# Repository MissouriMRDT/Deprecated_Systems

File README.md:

<<<<<<< HEAD
# Deprecated-Systems
 Deprecated sub-system repositories that have no present day equivalent

How to add repos to this: 

1) Make branch on here for the repo you're about to copy in
2) Clone this repo onto your pc
3) Make sure that you've merged all branches on the deprecated repo into master, this process only preserves its master
4) in gitshell inside of the Deprecated-Systems folder:

git checkout [name of branch you're going to copy the repo into]

git remote add x [url of deprecated repo]

git fetch x

git merge x/master --allow-unrelated-histories

git remote rm x

5) delete old branch

=======
Battery-Management-System
=========================

Battery Management System with integrated CC and CV charge control and passive cell balancing.
>>>>>>> x/master

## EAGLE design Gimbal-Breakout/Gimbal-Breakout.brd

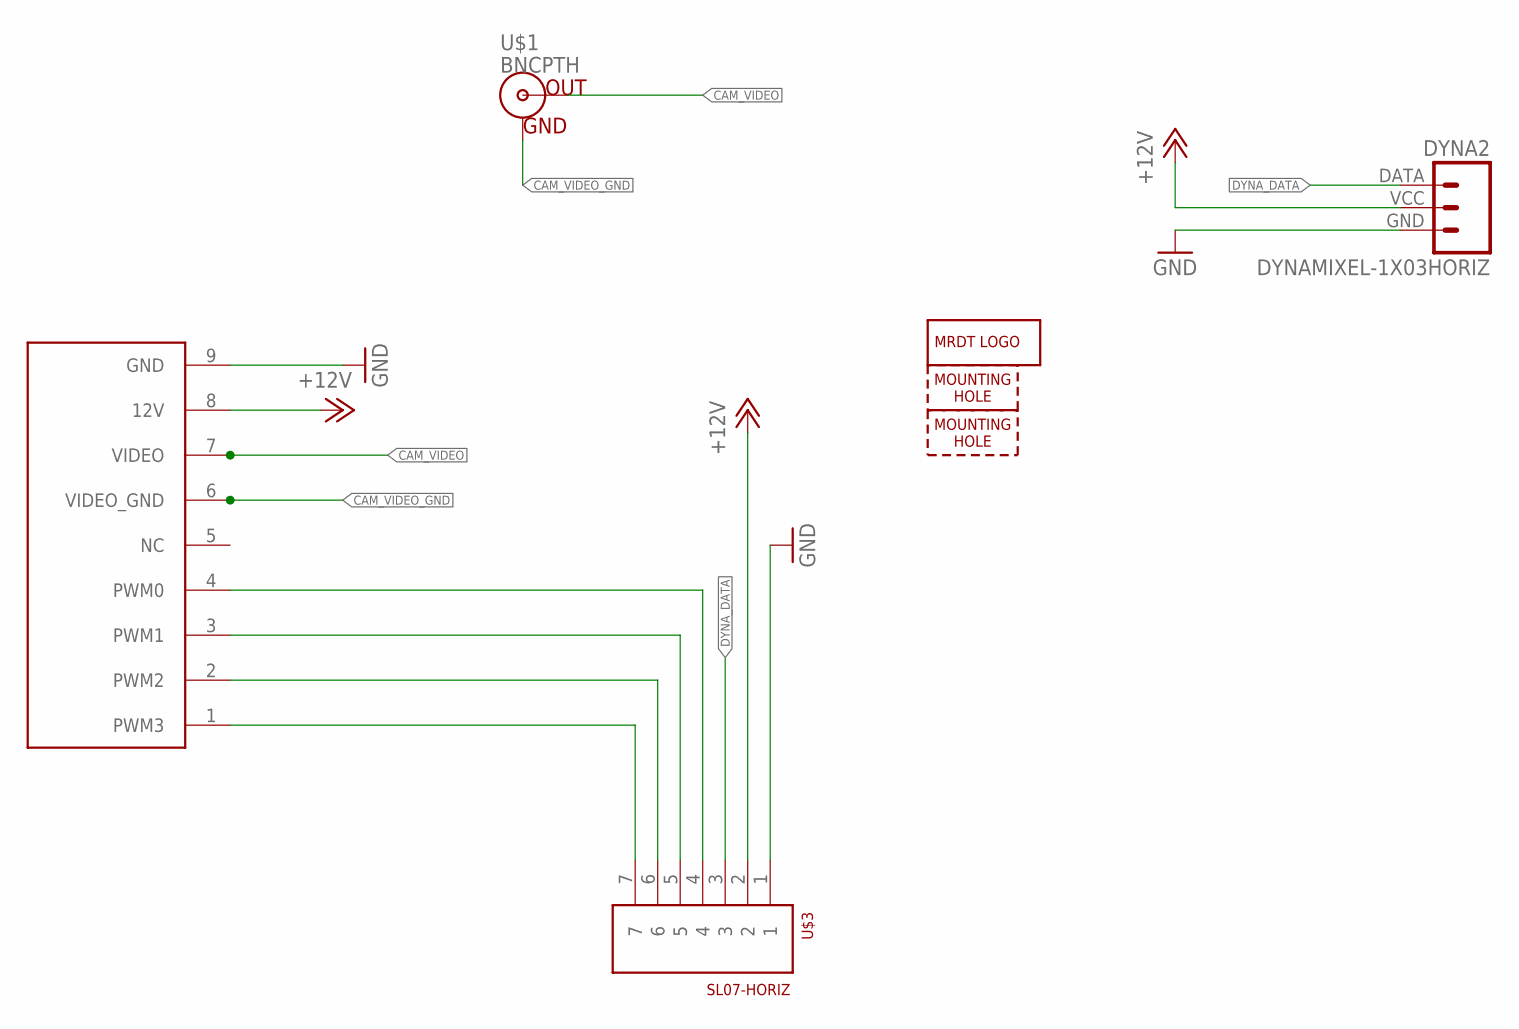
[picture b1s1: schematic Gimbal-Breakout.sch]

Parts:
DYNA2: DYNAMIXEL-1X03HORIZ; MLX-SPOX5268-3PIN
H1, H2: MOUNTING_HOLE#4; #4_SCREW
LOGO1: MRDT_LOGO
U$1: BNCPTH; BNC
U$3: SL07-HORIZ; MOLEX-70551-0006
U$4: CAMERA_BREAKOUT; CAM_CONNECTOR

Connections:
+12V: DYNA2.VCC, U$3.2, U$4.8 (12V)
CAM_PWM0: U$3.4, U$4.4 (PWM0)
CAM_PWM1: U$3.5, U$4.3 (PWM1)
CAM_PWM2: U$3.6, U$4.2 (PWM2)
CAM_PWM3: U$3.7, U$4.1 (PWM3)
CAM_VIDEO: U$1.S (OUT), U$4.7 (VIDEO)
CAM_VIDEO_GND: U$1.GND, U$4.6 (VIDEO_GND)
DYNA_DATA: DYNA2.DATA, U$3.3
GND: DYNA2.GND, U$3.1, U$4.9 (GND)

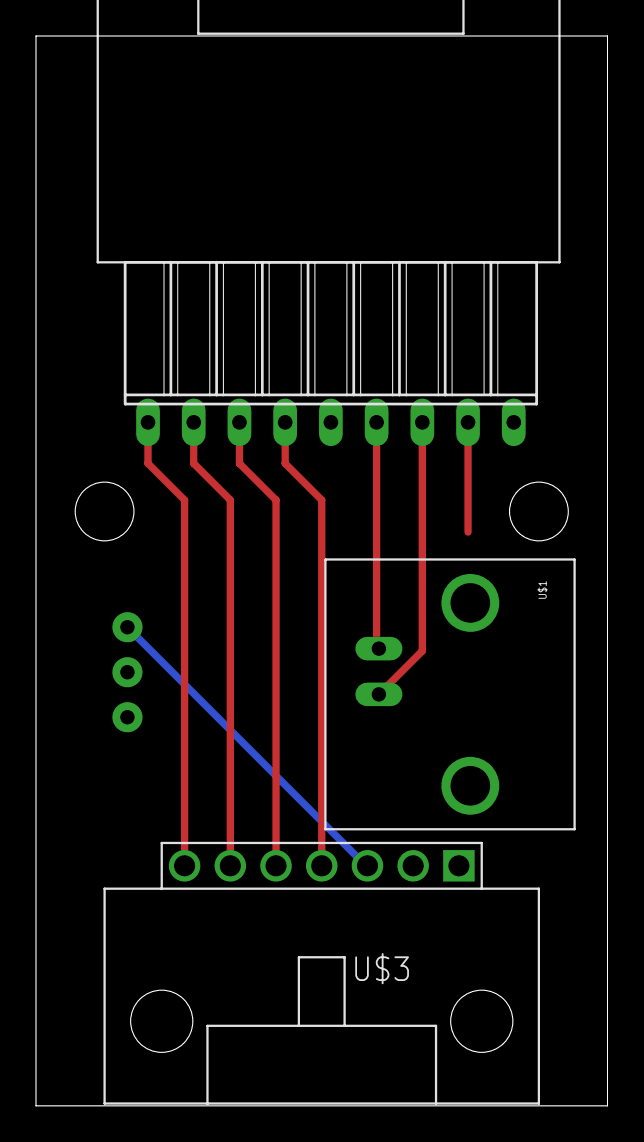
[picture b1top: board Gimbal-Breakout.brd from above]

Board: 2 copper layers, 31.8 x 59.4 mm, 7 parts (1 on the bottom side), 9 nets.

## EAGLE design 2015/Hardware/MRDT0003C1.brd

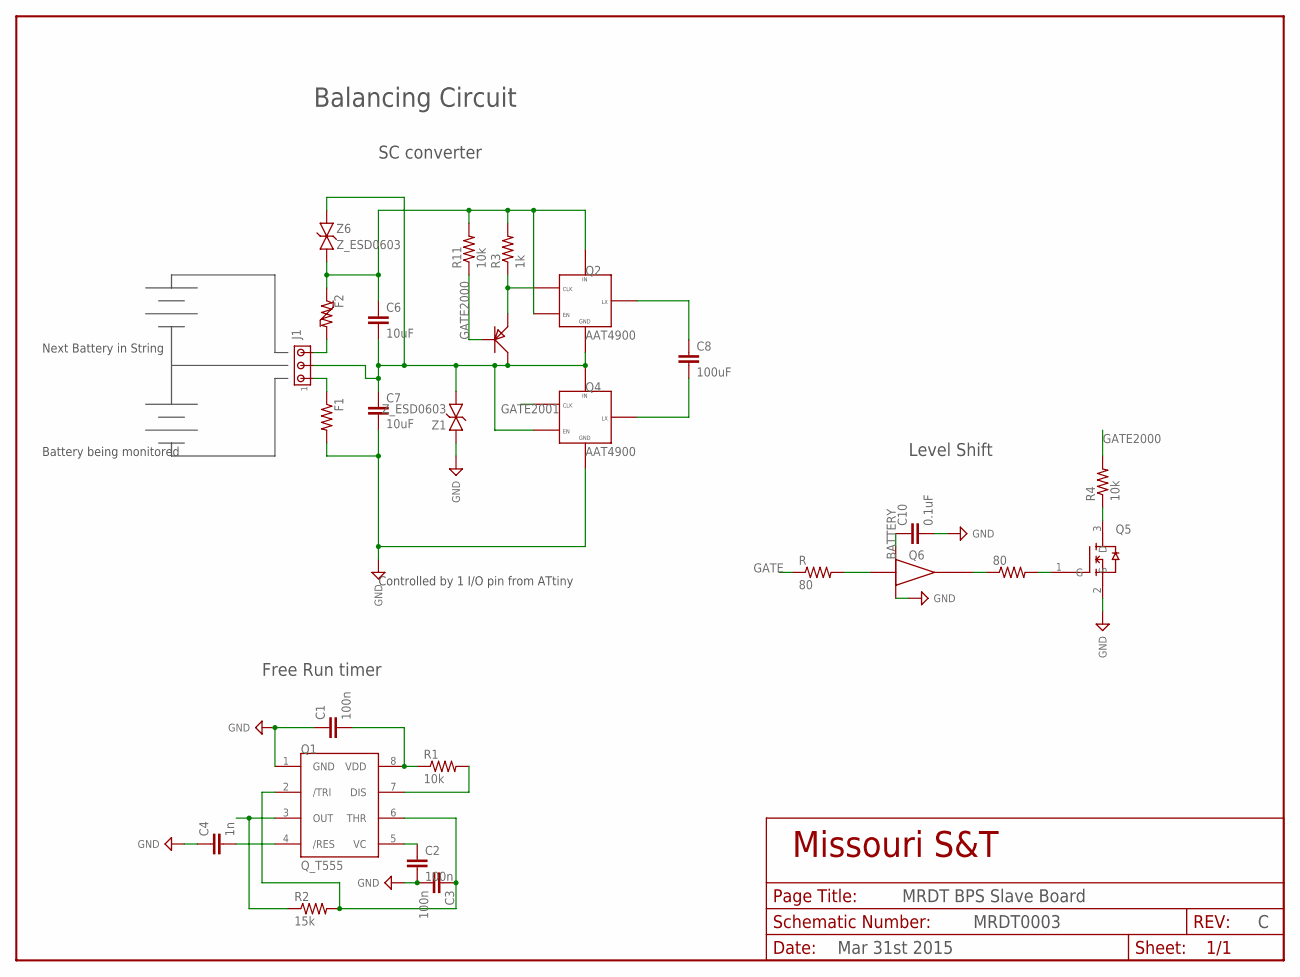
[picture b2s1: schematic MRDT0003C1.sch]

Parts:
80: R_RES_1206; R_1206
C1, C2, C3: 100n; C_0603
C4: 1n; C_0603
C6, C7: 10uF; C_1206
C8: 100uF; C_1206
C10: 0.1uF; C_0603
F1, F2: R_RES_1210; R_1210
J1: J_HDR1X3_BRK_100MIL; J_BRK1X3_100MIL
Q1: Q_T555; SOIC8
Q2, Q4: AAT4900; SOT-23-5
Q5: N-CH-MOSFETSOT-23; SOT-23
Q6: Q_INVERTERSOT-23-5; SOT-23-5
Q7: Q_PNP; SOT-23
R: 80; R_0603
R1, R4, R11: 10k; R_0603
R2: 15k; R_0603
R3: 1k; R_0603
Z1, Z6: Z_ESD0603; 0603

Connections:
BATTERY: C1.2, C4.2, C6.2, C7.1, C10.1, J1.2, Q1.4 (/RES), Q1.8 (VDD), Q2.2 (GND), Q4.3 (EN), Q4.5 (IN), Q6.5 (VCC), Q7.3 (C), R1.1, Z1.1, Z6.2
GATE: Q1.3 (OUT), R.1, R2.1
GATE2000: Q7.1 (B), R4.2, R11.1
GATE2001: Q4.4 (CLK), Q6.2 (A), R.2
GND: C1.1, C2.2, C3.2, C4.1, C7.2, C10.2, F1.2, Q1.1 (GND), Q4.2 (GND), Q5.2 (S), Q6.3 (GND), Z1.2
unnamed: Q2.4 (CLK), Q7.2 (E), R3.1
unnamed: F2.2, J1.3
unnamed: C8.1, Q2.1 (LX)
unnamed: C8.2, Q4.1 (LX)
unnamed: F1.1, J1.1
unnamed: Q1.7 (DIS), R1.2
unnamed: Q5.3 (D), R4.1
unnamed: 80.1, Q6.4 (Y)
unnamed: 80.2, Q5.1 (G)
unnamed: C6.1, F2.1, Q2.3 (EN), Q2.5 (IN), R3.2, R11.2, Z6.1
unnamed: C3.1, Q1.2 (/TRI), Q1.6 (THR), R2.2
unnamed: C2.1, Q1.5 (VC)

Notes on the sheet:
Battery being monitored
Next Battery in String
Controlled by 1 I/O pin from ATtiny
Balancing Circuit
SC converter
Level Shift
MRDT BPS Slave Board
MRDT0003
Mar 31st 2015
Free Run timer

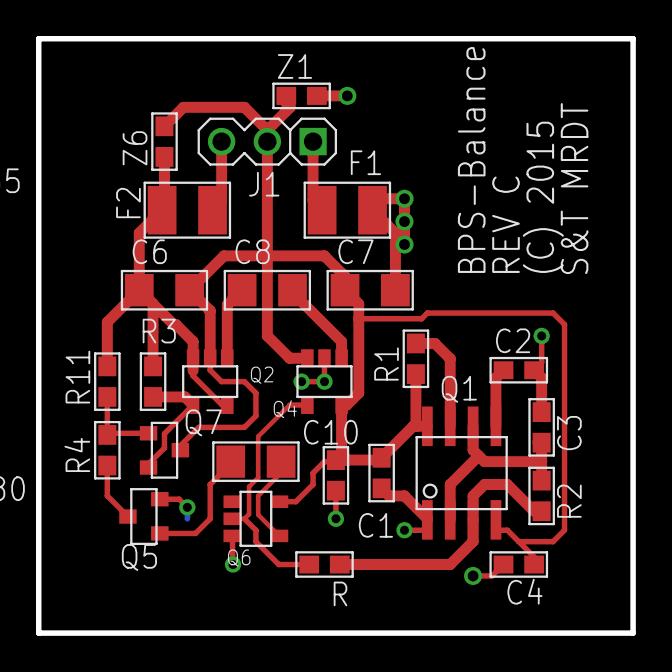
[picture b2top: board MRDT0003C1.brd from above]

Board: 2 copper layers, 33.0 x 33.0 mm, 26 parts (0 on the bottom side), 17 nets.

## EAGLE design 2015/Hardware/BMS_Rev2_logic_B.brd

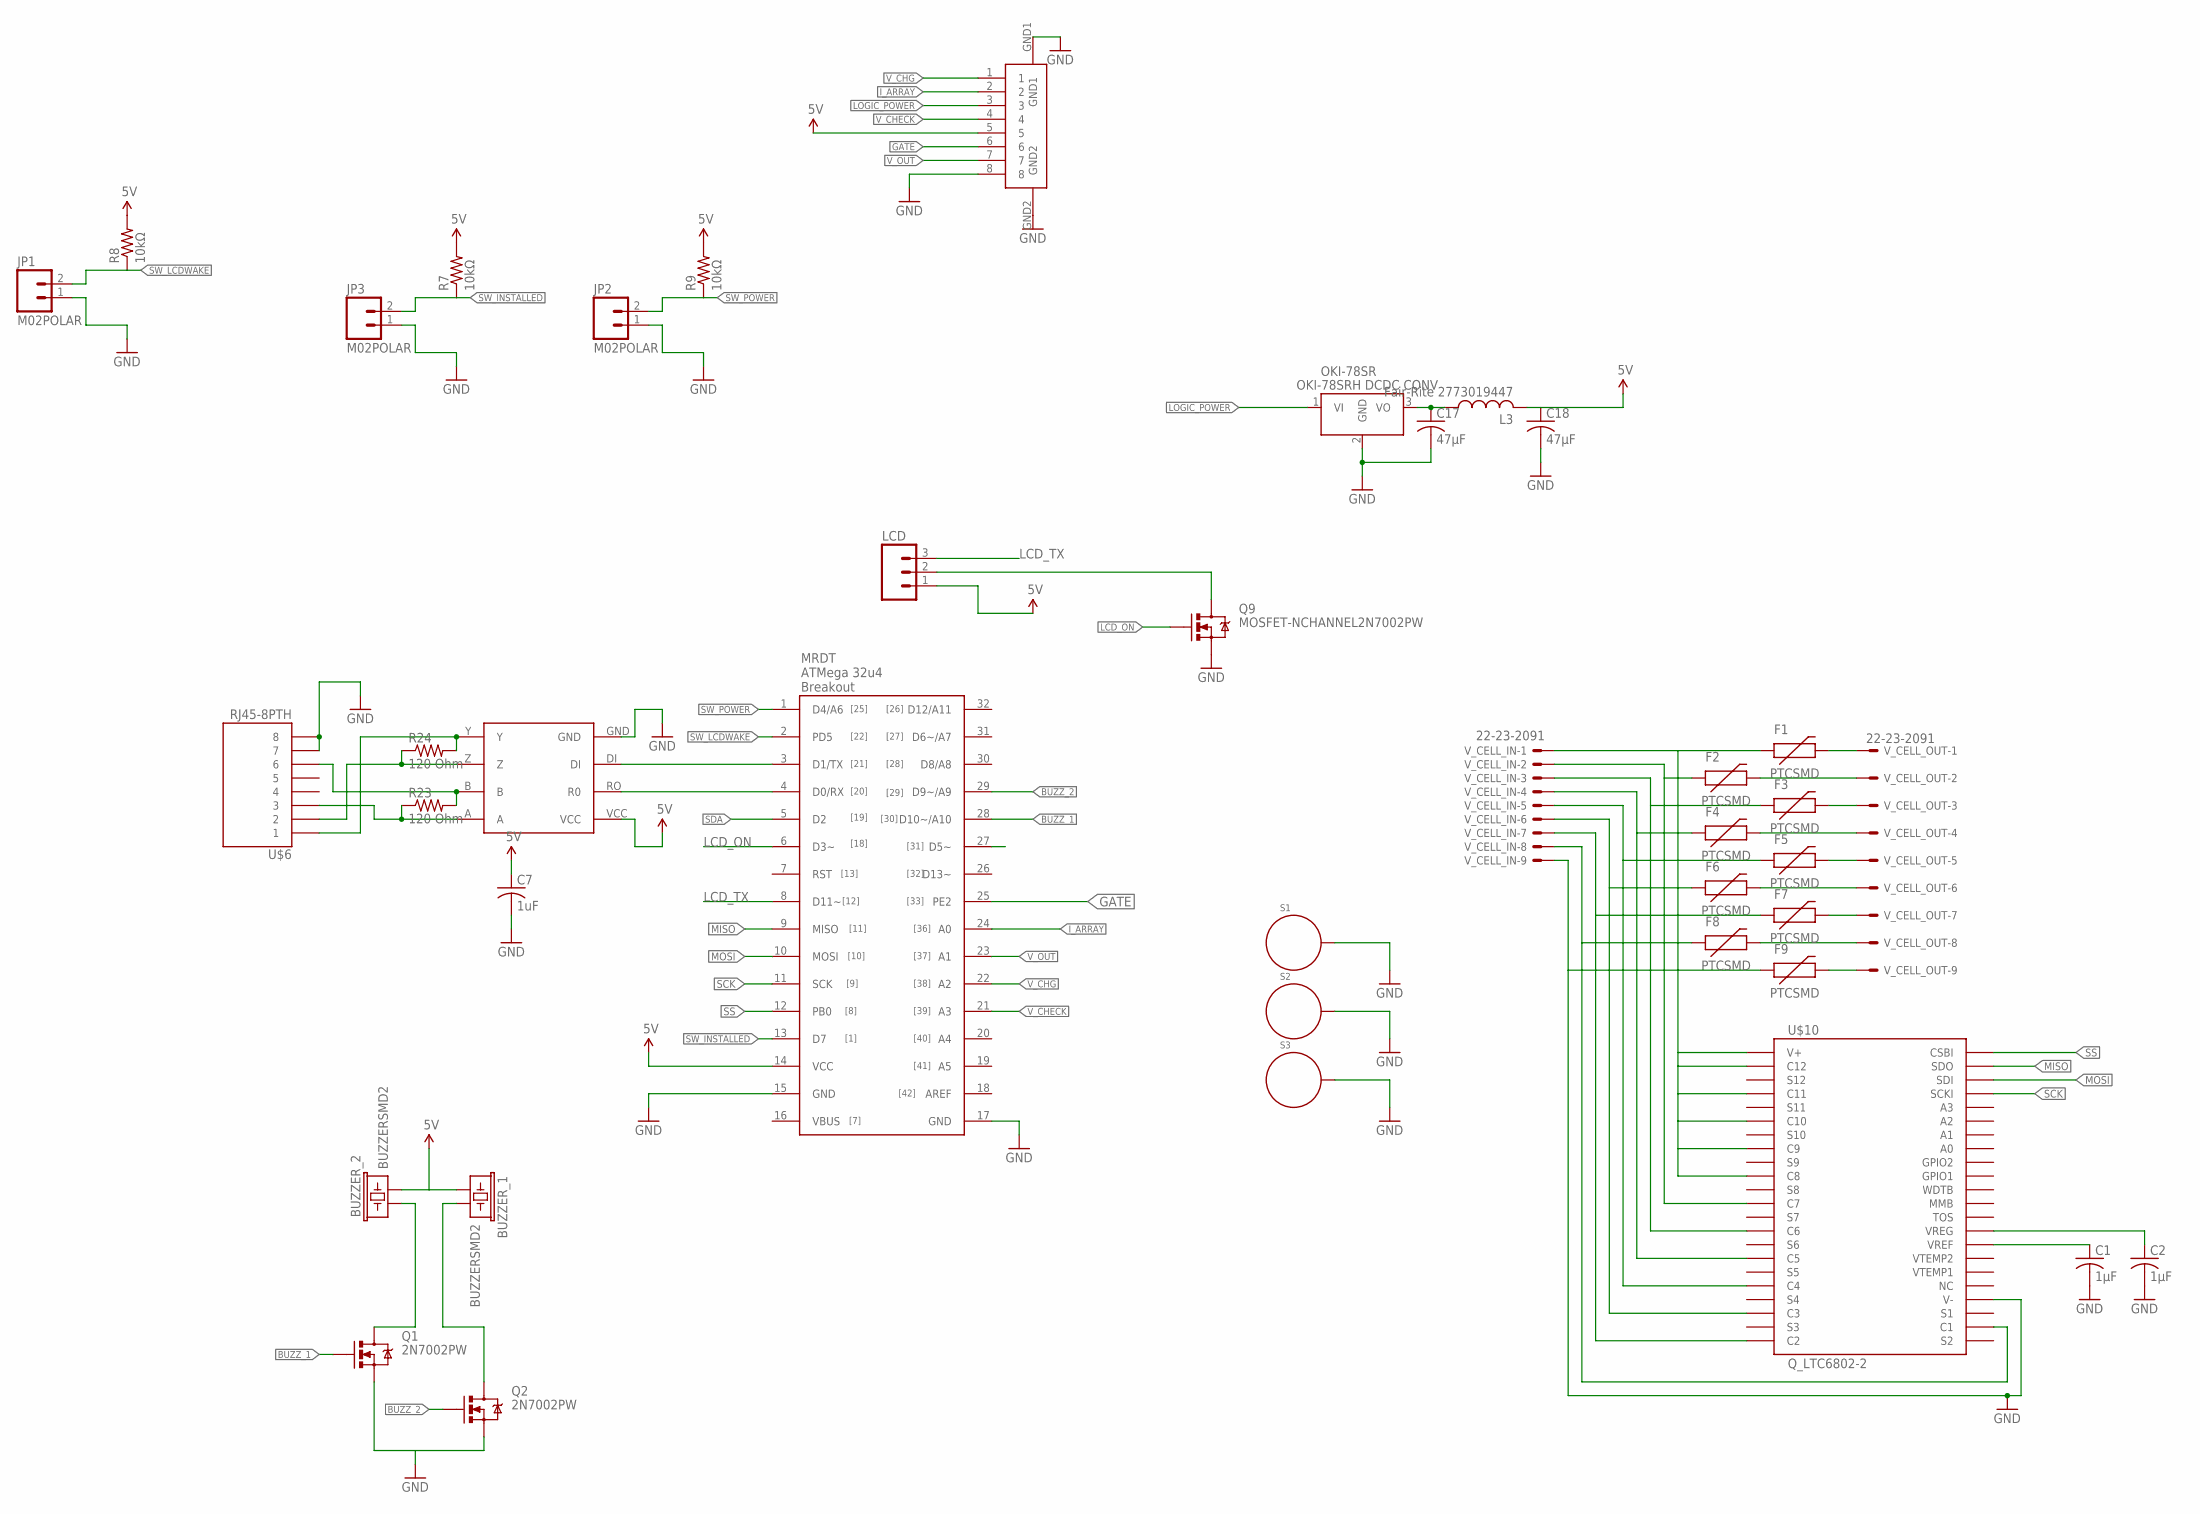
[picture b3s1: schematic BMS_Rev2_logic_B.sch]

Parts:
BUZZER_1, BUZZER_2: BUZZERSMD2; BUZZER-CCV
C1, C2: 1µF; C1206
C7: 1uF; C1206
C17, C18: 47µF; C1206
F1, F2, F3, F4, F5, F6, F7, F8, F9: PTCSMD; PTC-1206
JP1, JP2, JP3: M02POLAR; MOLEX-1X2
L3: Fair-Rite 2773019447; L4532M
LCD: M03POLAR; MOLEX-1X3
OKI-78SR: Q_OKI-78SR; OKI-78SRH
Q1, Q2: 2N7002PW; SOT323
Q9: MOSFET-NCHANNEL2N7002PW; SOT323
R7, R8, R9: 10kΩ; R1206
R23, R24: 120 Ohm; 1206
S1, S2, S3: STANDOFF_ELECTRICAL; STANDOFF-ELECTRICAL
U$1: 8POS_LOGIC; LOGIC_CONNECT
U$3: 32U4_BREAKOUT; 32U4_MCU_DIP
U$6: RJ45-8PTH; RJ45-8
U$9: MAX3077; MAX3070E
U$10: Q_LTC6802-2; SSOP44
V_CELL_IN: 22-23-2091
V_CELL_OUT: 22-23-2091

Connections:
5V: BUZZER_1.+ (1), BUZZER_2.- (2), C7.1, C18.1, L3.2, LCD.1, R7.2, R8.2, R9.2, U$1.5, U$3.14 (VCC), U$9.VCC
BUZZ_1: Q1.1 (G), U$3.28 (D10~/A10)
BUZZ_2: Q2.1 (G), U$3.29 (D9~/A9)
GATE: U$1.6, U$3.25 (PE2)
GND: C1.2, C2.2, C7.2, C17.2, C18.2, F9.1, JP1.1, JP2.1, JP3.1, OKI-78SR.2 (GND), Q1.2 (S), Q2.2 (S), Q9.2 (S), S1.P1, S2.P1, S3.P1, U$1.8, U$1.GND1, U$1.GND2, U$3.15 (GND), U$3.17 (GND), U$6.7, U$6.8, U$9.GND, U$10.26 (V-), V_CELL_IN.9
I_ARRAY: U$1.2, U$3.24 (A0)
LCD_DB4: U$3.27 (D5~)
LCD_ON: Q9.1 (G), U$3.6 (D3~)
LCD_TX: LCD.3, U$3.8 (D11~)
LOGIC_POWER: OKI-78SR.1 (VI), U$1.3
MISO: U$3.9 (MISO), U$10.43 (SDO)
MOSI: U$3.10 (MOSI), U$10.42 (SDI)
unnamed: F1.2, V_CELL_OUT.1
unnamed: F2.2, V_CELL_OUT.2
unnamed: F3.2, V_CELL_OUT.3
unnamed: F9.2, V_CELL_OUT.9
unnamed: LCD.2, Q9.3 (D)
unnamed: R24.2, U$6.1, U$9.Y
unnamed: R24.1, U$6.2, U$9.Z
unnamed: BUZZER_1.- (2), Q2.3 (D)
unnamed: R23.2, U$6.6, U$9.B
unnamed: R23.1, U$6.3, U$9.A
unnamed: U$3.3 (D1/TX), U$9.DI
unnamed: C1.1, U$10.30 (VREF)
unnamed: C2.1, U$10.31 (VREG)
unnamed: F4.2, V_CELL_OUT.4
unnamed: F5.2, V_CELL_OUT.5
unnamed: F6.2, V_CELL_OUT.6
unnamed: F7.2, V_CELL_OUT.7
unnamed: F8.2, V_CELL_OUT.8
unnamed: BUZZER_2.+ (1), Q1.3 (D)
unnamed: F1.1, U$10.1 (V+), U$10.2 (C12), U$10.4 (C11), U$10.6 (C10), U$10.8 (C9), U$10.10 (C8), V_CELL_IN.1
unnamed: F2.1, U$10.12 (C7), V_CELL_IN.2
unnamed: F3.1, U$10.14 (C6), V_CELL_IN.3
unnamed: F6.1, U$10.20 (C3), V_CELL_IN.6
unnamed: F7.1, U$10.22 (C2), V_CELL_IN.7
unnamed: F8.1, U$10.24 (C1), V_CELL_IN.8
unnamed: F4.1, U$10.16 (C5), V_CELL_IN.4
unnamed: F5.1, U$10.18 (C4), V_CELL_IN.5
unnamed: C17.1, L3.1, OKI-78SR.3 (VO)
RXD: U$3.4 (D0/RX), U$9.RO (R0)
SCK: U$3.11 (SCK), U$10.41 (SCKI)
SDA: U$3.5 (D2)
SS: U$3.12 (PB0), U$10.44 (CSBI)
SW_INSTALLED: JP3.2, R7.1, U$3.13 (D7)
SW_LCDWAKE: JP1.2, R8.1, U$3.2 (PD5)
SW_POWER: JP2.2, R9.1, U$3.1 (D4/A6)
V_CHECK: U$1.4, U$3.21 (A3)
V_CHG: U$1.1, U$3.22 (A2)
V_OUT: U$1.7, U$3.23 (A1)

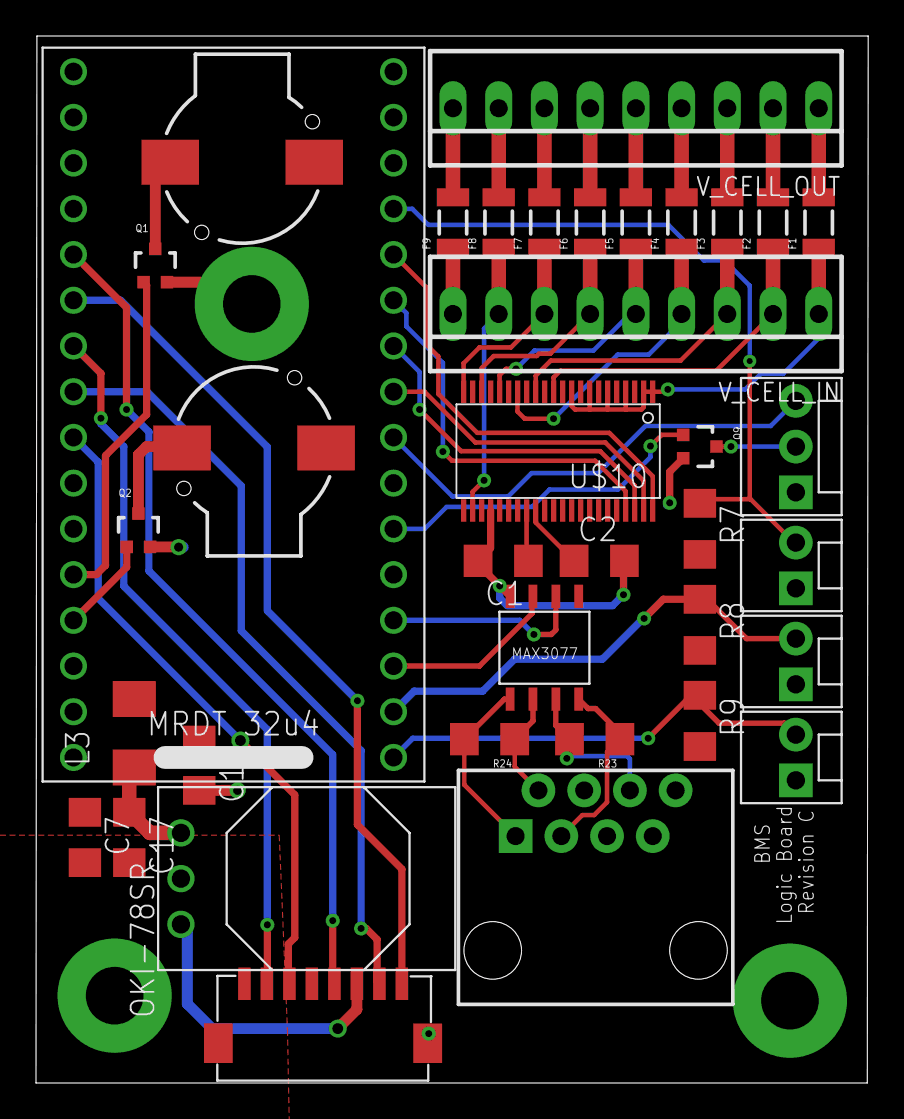
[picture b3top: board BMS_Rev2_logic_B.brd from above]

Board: 2 copper layers, 46.2 x 58.2 mm, 40 parts (0 on the bottom side), 48 nets.

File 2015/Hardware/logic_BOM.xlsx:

Quantity | Value | Device | Package | DigiKey ID
1 |  | L-USL3216C
1 | 32U4_BREAKOUT | 32U4_BREAKOUT
1 | MAX3077 | MAX3077 |  | MAX3077EESA+-ND
1 | MOSFET-NCHANNEL2N7002PW | MOSFET-NCHANNEL2N7002PW |  | 568-5987-1-ND
1 | Q_LTC6802-2 | Q_LTC6802-2 |  | LTC6802IG-2#PBF-ND
1 | Q_OKI-78SR | Q_OKI-78SR |  | 811-2692-ND
1 | RJ45-8PTH | RJ45-8PTH |  | 609-1046-ND
2 | 120 Ohm | RESISTOR1206 |  | P120ECT-ND
3 | 1uF | C-USC1206 |  | 445-1592-1-ND
2 | 22-23-2091 | 22-23-2091 |  | WM4207-ND
2 | 47uF | C-USC1206 |  | 490-5528-1-ND
2 |  | BUZZERSMD2 |  | 102-1265-1-ND
3 | 10k | R-US_R1206 |  | P10KECT-ND
9 |  | PTCSMD |  | 283-3134-1-ND

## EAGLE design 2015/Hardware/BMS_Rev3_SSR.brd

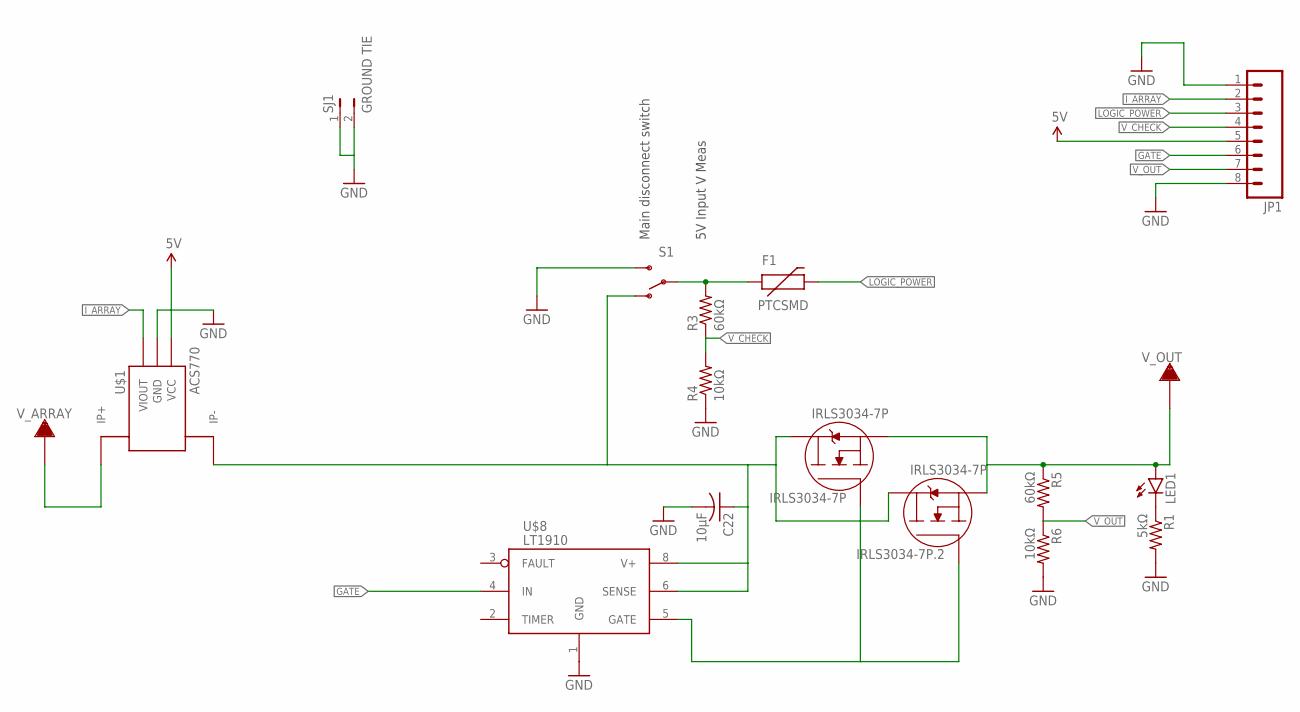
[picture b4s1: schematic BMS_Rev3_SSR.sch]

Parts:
C22: 10µF; C1206
F1: PTCSMD; PTC-1206
IRLS3034-7P, IRLS3034-7P.2: IRLS3034-7P; D2PAK-7
JP1: M08BM08B-SRSS-TB; BM08B-SRSS-TB
LED1: LED1206; LED-1206
R1: 5kΩ; R1206
R3, R5: 60kΩ; R1206
R4, R6: 10kΩ; R1206
S1: SWITCH-SPDTPTH; SWITCH-SPDT
SJ1: GROUND TIE; PTH-JUMPER-2-NO_NO_SILK
U$1: ACS770; PFF_LEADFORM
U$8: LT1910; SO8
V_ARRAY: TERMINAL_HOLE; LARGE_TERMINAL_HOLE
V_OUT: TERMINAL_HOLE; LARGE_TERMINAL_HOLE

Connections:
5V: JP1.5, U$1.1 (VCC)
GATE: JP1.6, U$8.4 (IN)
GND: C22.2, JP1.1, JP1.8, R1.2, R4.1, R6.2, S1.3 (S), SJ1.1, SJ1.2, U$1.2 (GND), U$8.1 (GND)
I_ARRAY: JP1.2, U$1.3 (VIOUT)
LOGIC_POWER: F1.2, JP1.3
unnamed: IRLS3034-7P.2 (SOURCE), IRLS3034-7P.3 (SOURCE), IRLS3034-7P.4 (SOURCE), IRLS3034-7P.5 (SOURCE), IRLS3034-7P.6 (SOURCE), IRLS3034-7P.2.2 (SOURCE), IRLS3034-7P.2.3 (SOURCE), IRLS3034-7P.2.4 (SOURCE), IRLS3034-7P.2.5 (SOURCE), IRLS3034-7P.2.6 (SOURCE), LED1.A, R5.1, V_OUT.P$1
unnamed: U$1.4_1 (IP+), U$1.4_2 (IP+), U$1.4_3 (IP+), U$1.4_4 (IP+), U$1.4_5 (IP+), U$1.4_6 (IP+), U$1.4_7 (IP+), U$1.4_8 (IP+), U$1.4_9 (IP+), U$1.4_10 (IP+), U$1.4_11 (IP+), U$1.4_12 (IP+), U$1.4_13 (IP+), U$1.4_14 (IP+), U$1.4_15 (IP+), U$1.4_16 (IP+), U$1.4_B (IP+), U$1.4_T (IP+), V_ARRAY.P$1
unnamed: C22.1, IRLS3034-7P.PAD (DRAIN), IRLS3034-7P.2.PAD (DRAIN), S1.1 (O), U$1.5_1 (IP-), U$1.5_2 (IP-), U$1.5_3 (IP-), U$1.5_4 (IP-), U$1.5_5 (IP-), U$1.5_6 (IP-), U$1.5_7 (IP-), U$1.5_8 (IP-), U$1.5_9 (IP-), U$1.5_10 (IP-), U$1.5_11 (IP-), U$1.5_12 (IP-), U$1.5_13 (IP-), U$1.5_14 (IP-), U$1.5_15 (IP-), U$1.5_16 (IP-), U$1.5_B (IP-), U$1.5_T (IP-), U$8.6 (SENSE), U$8.8 (V+)
unnamed: LED1.C, R1.1
unnamed: IRLS3034-7P.1 (GATE), IRLS3034-7P.2.1 (GATE), U$8.5 (GATE)
unnamed: F1.1, R3.2, S1.2
V_CHECK: JP1.4, R3.1, R4.2
V_OUT: JP1.7, R5.2, R6.1

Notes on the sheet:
5V Input V Meas
Main disconnect switch

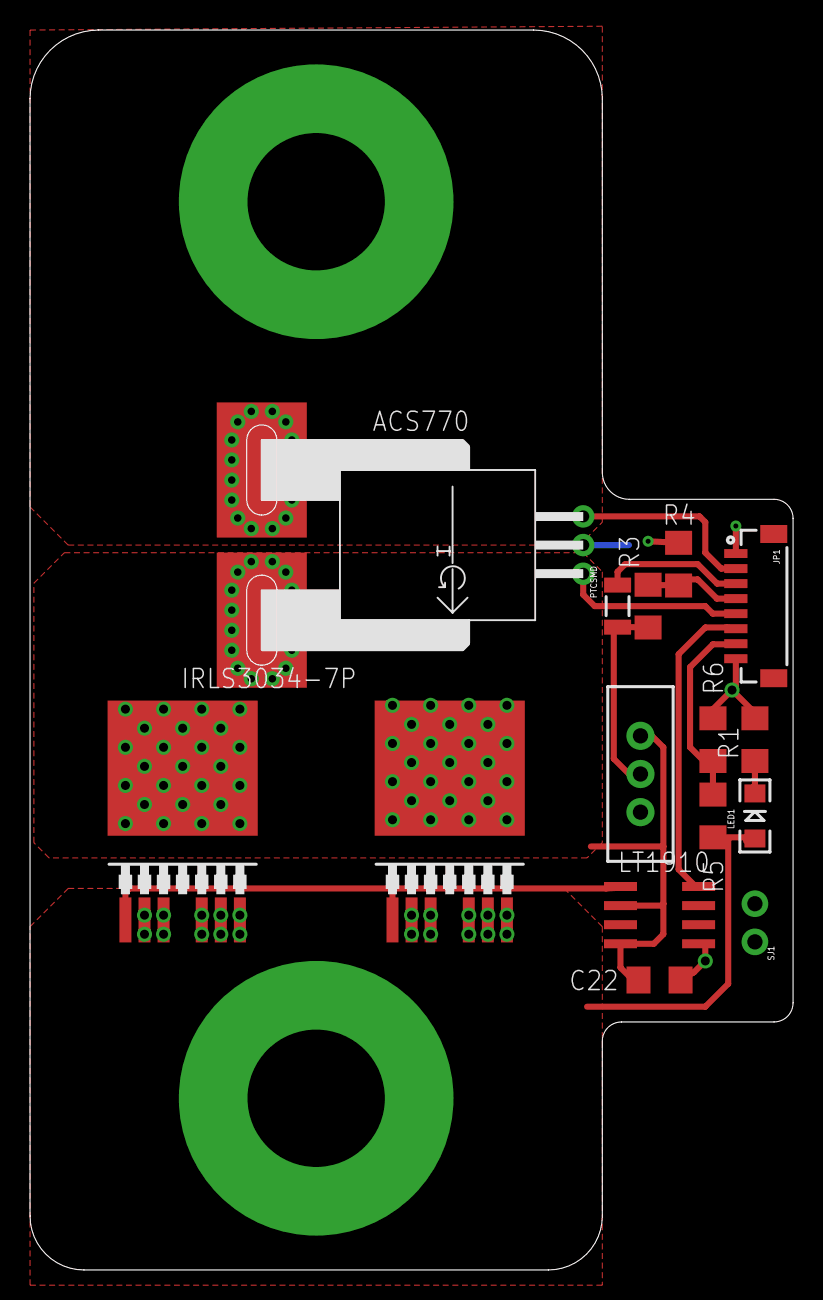
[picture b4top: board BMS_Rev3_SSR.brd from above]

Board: 2 copper layers, 50.8 x 82.5 mm, 17 parts (0 on the bottom side), 13 nets.

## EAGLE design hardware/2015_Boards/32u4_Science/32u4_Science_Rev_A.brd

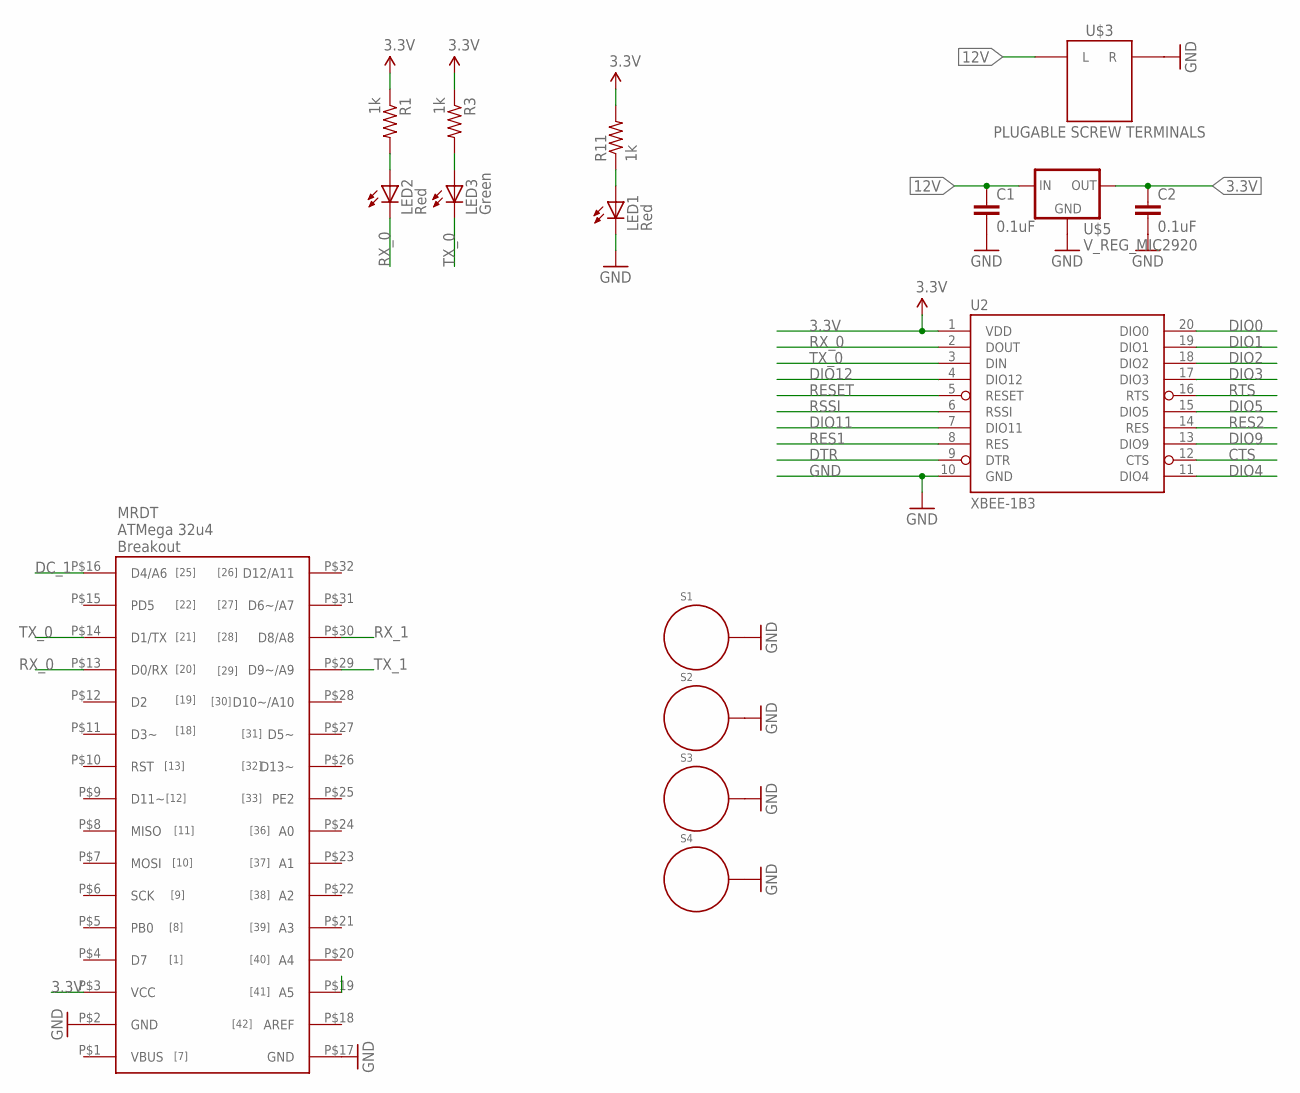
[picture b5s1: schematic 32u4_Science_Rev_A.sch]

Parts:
C1, C2: 0.1uF; 1206
LED1, LED2: Red; LED-0603
LED3: Green; LED-0603
R1, R3, R11: 1k; 1206
S1, S2, S3, S4: STANDOFF_ELECTRICAL; STANDOFF-ELECTRICAL
U2: XBEE-1B3; XBEE-SMD
U$1: 32U4_BREAKOU_SMD; 32U3_MCU_DIP_SMD
U$3: PLUGABLE SCREW TERMINALS; 691321100002
U$5: V_REG_MIC2920; SOT223

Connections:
3.3V: C2.1, R1.1, R3.1, R11.2, U2.1 (VDD), U$1.P$3 (VCC), U$5.3 (OUT)
12V: C1.1, U$3.L, U$5.1 (IN)
CTS: U2.12 (CTS)
DC_1: U$1.P$16 (D4/A6)
DIO0: U2.20 (DIO0)
DIO1: U2.19 (DIO1)
DIO2: U2.18 (DIO2)
DIO3: U2.17 (DIO3)
DIO4: U2.11 (DIO4)
DIO5: U2.15 (DIO5)
DIO9: U2.13 (DIO9)
DIO11: U2.7 (DIO11)
DIO12: U2.4 (DIO12)
DTR: U2.9 (DTR)
GND: C1.2, C2.2, LED1.C, S1.P1, S2.P1, S3.P1, S4.P1, U2.10 (GND), U$1.P$2 (GND), U$1.P$17 (GND), U$3.R, U$5.2 (GND), U$5.4 (GND)
unnamed: LED2.A, R1.2
unnamed: LED3.A, R3.2
unnamed: LED1.A, R11.1
RES1: U2.8 (RES)
RES2: U2.14 (RES)
RESET: U2.5 (RESET)
RSSI: U2.6 (RSSI)
RTS: U2.16 (RTS)
RX_0: LED2.C, U2.2 (DOUT), U$1.P$13 (D0/RX)
RX_1: U$1.P$30 (D8/A8)
TX_0: LED3.C, U2.3 (DIN), U$1.P$14 (D1/TX)
TX_1: U$1.P$29 (D9~/A9)

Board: 2 copper layers, 16 parts (1 on the bottom side), 8 nets, no tracks yet.

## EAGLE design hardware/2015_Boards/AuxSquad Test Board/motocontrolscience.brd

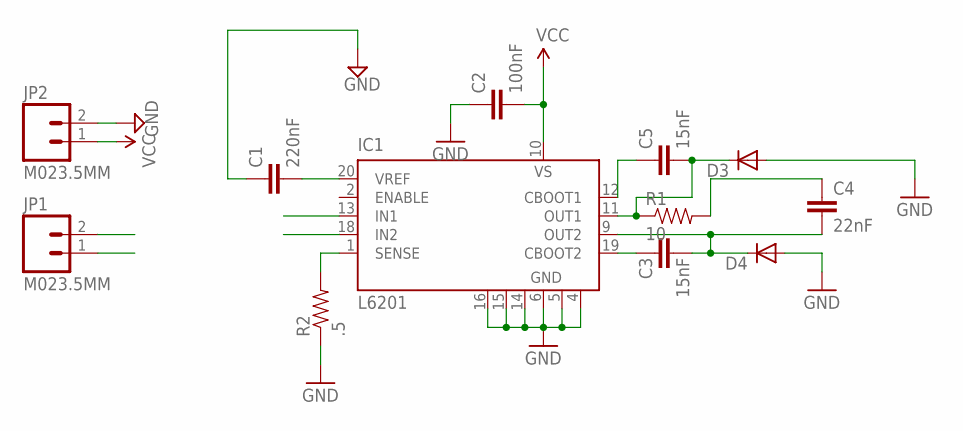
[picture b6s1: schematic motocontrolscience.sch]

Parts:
C1: 220nF; 1206
C2: 100nF; 1206
C3, C5: 15nF; 1206
C4: 22nF; 1206
D3, D4: DIODE-DO214BA; DO214BA
IC1: L6201; SO20
JP1, JP2: M023.5MM; SCREWTERMINAL-3.5MM-2
R1: 10; 1206
R2: .5; 1206

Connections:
GND: C1.1, C2.1, D3.A, D4.A, IC1.4 (GND), IC1.5 (GND), IC1.6 (GND), IC1.14 (GND), IC1.15 (GND), IC1.16 (GND), JP2.2, R2.1
unnamed: C3.1, IC1.19 (CBOOT2)
unnamed: C4.1, R1.2
unnamed: C5.1, IC1.12 (CBOOT1)
unnamed: C1.2, IC1.20 (VREF)
unnamed: IC1.1 (SENSE), R2.2
OUT1: C5.2, D3.C, IC1.11 (OUT1), JP1.1, R1.1
OUT2: C3.2, C4.2, D4.C, IC1.9 (OUT2), JP1.2
VCC: C2.2, IC1.10 (VS), JP2.1

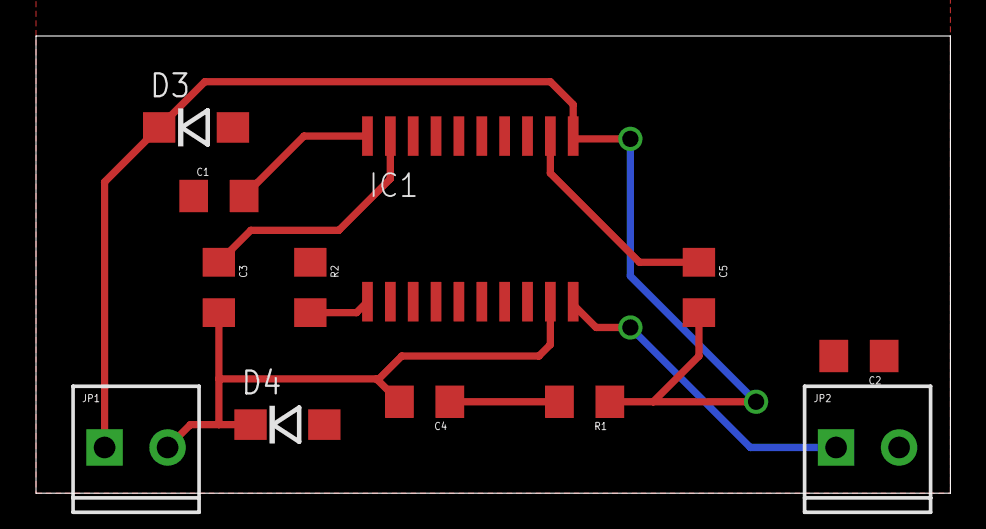
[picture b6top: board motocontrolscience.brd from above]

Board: 2 copper layers, 50.8 x 25.4 mm, 12 parts (0 on the bottom side), 9 nets.

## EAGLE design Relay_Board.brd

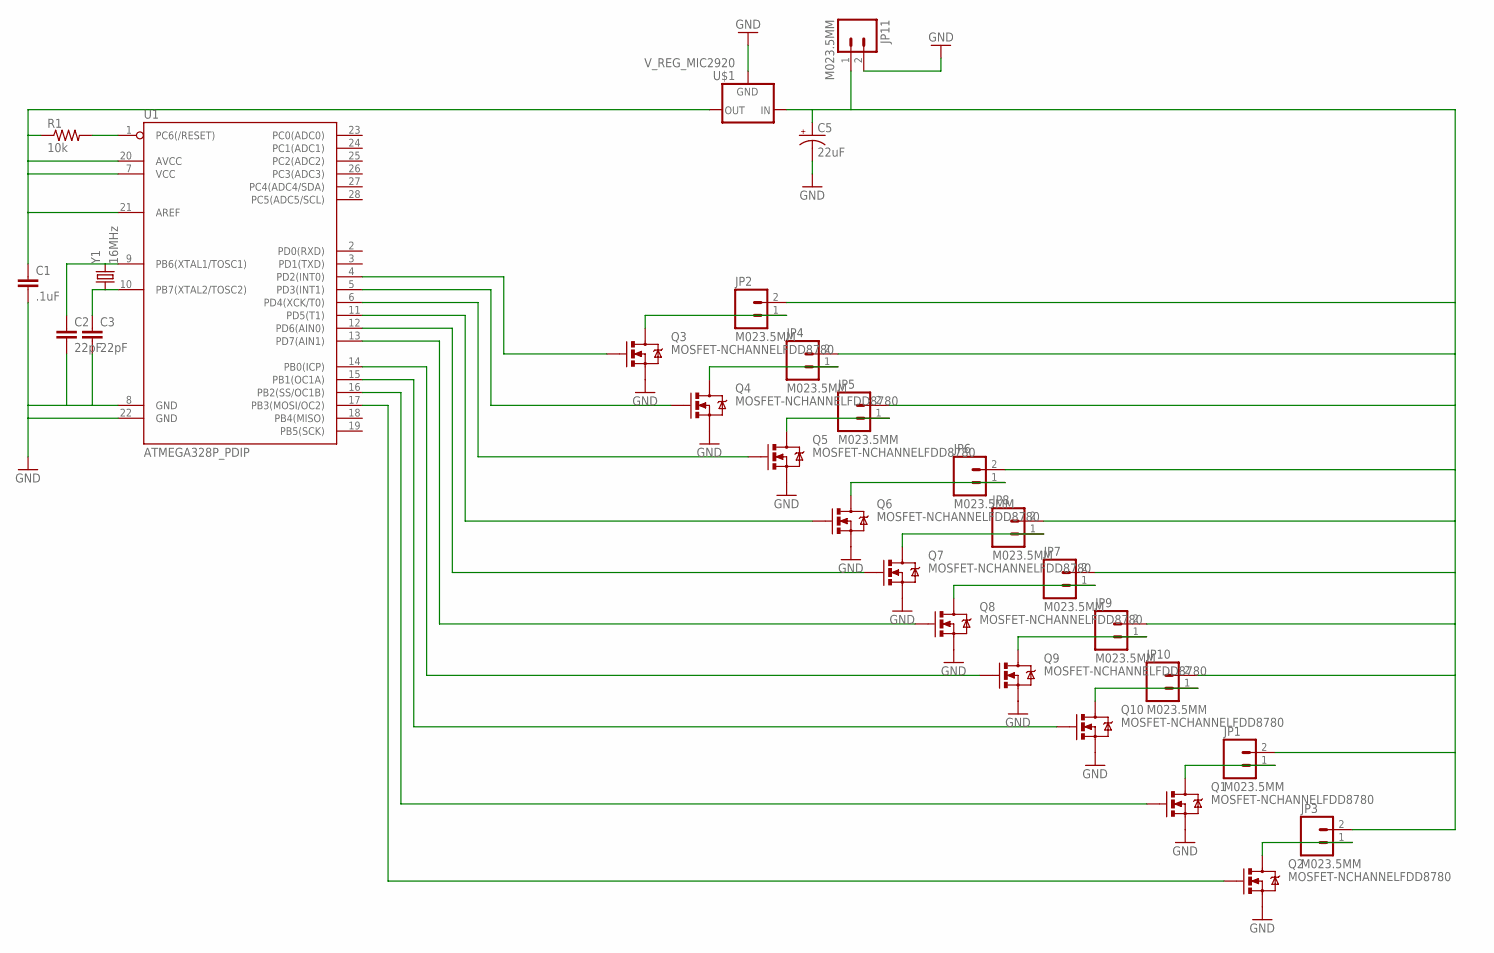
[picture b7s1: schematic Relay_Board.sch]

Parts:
C1: .1uF; 1206
C2, C3: 22pF; 1206
C5: 22uF; PANASONIC_C
JP1, JP2, JP3, JP4, JP5, JP6, JP7, JP8, JP9, JP10, JP11: M023.5MM; SCREWTERMINAL-3.5MM-2
Q1, Q2, Q3, Q4, Q5, Q6, Q7, Q8, Q9, Q10: MOSFET-NCHANNELFDD8780; DPAK
R1: 10k; 1206
U1: ATMEGA328P_PDIP; DIL28-3
U$1: V_REG_MIC2920; SOT223
Y1: 16MHz; CRYSTAL-SMD-5X3

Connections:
12V: C5.+, JP1.2, JP2.2, JP3.2, JP4.2, JP5.2, JP6.2, JP7.2, JP8.2, JP9.2, JP10.2, JP11.1, U$1.1 (IN)
GND: C1.2, C2.2, C3.2, C5.-, JP11.2, Q1.3 (S), Q2.3 (S), Q3.3 (S), Q4.3 (S), Q5.3 (S), Q6.3 (S), Q7.3 (S), Q8.3 (S), Q9.3 (S), Q10.3 (S), U1.8 (GND), U1.22 (GND), U$1.2 (GND)
unnamed: Q1.1 (G), U1.16 (PB2(SS/OC1B))
unnamed: R1.2, U1.1 (PC6(/RESET))
unnamed: C2.1, U1.9 (PB6(XTAL1/TOSC1)), Y1.3 (2)
unnamed: C3.1, U1.10 (PB7(XTAL2/TOSC2)), Y1.1
unnamed: Q2.1 (G), U1.17 (PB3(MOSI/OC2))
unnamed: JP1.1, Q1.4 (D)
unnamed: JP3.1, Q2.4 (D)
unnamed: JP2.1, Q3.4 (D)
unnamed: Q3.1 (G), U1.4 (PD2(INT0))
unnamed: Q4.1 (G), U1.5 (PD3(INT1))
unnamed: JP4.1, Q4.4 (D)
unnamed: JP5.1, Q5.4 (D)
unnamed: Q5.1 (G), U1.6 (PD4(XCK/T0))
unnamed: JP6.1, Q6.4 (D)
unnamed: Q7.1 (G), U1.12 (PD6(AIN0))
unnamed: JP8.1, Q7.4 (D)
unnamed: JP7.1, Q8.4 (D)
unnamed: Q8.1 (G), U1.13 (PD7(AIN1))
unnamed: Q9.1 (G), U1.14 (PB0(ICP))
unnamed: JP9.1, Q9.4 (D)
unnamed: JP10.1, Q10.4 (D)
unnamed: Q10.1 (G), U1.15 (PB1(OC1A))
unnamed: Q6.1 (G), U1.11 (PD5(T1))
unnamed: C1.1, R1.1, U1.7 (VCC), U1.20 (AVCC), U1.21 (AREF), U$1.3 (OUT)

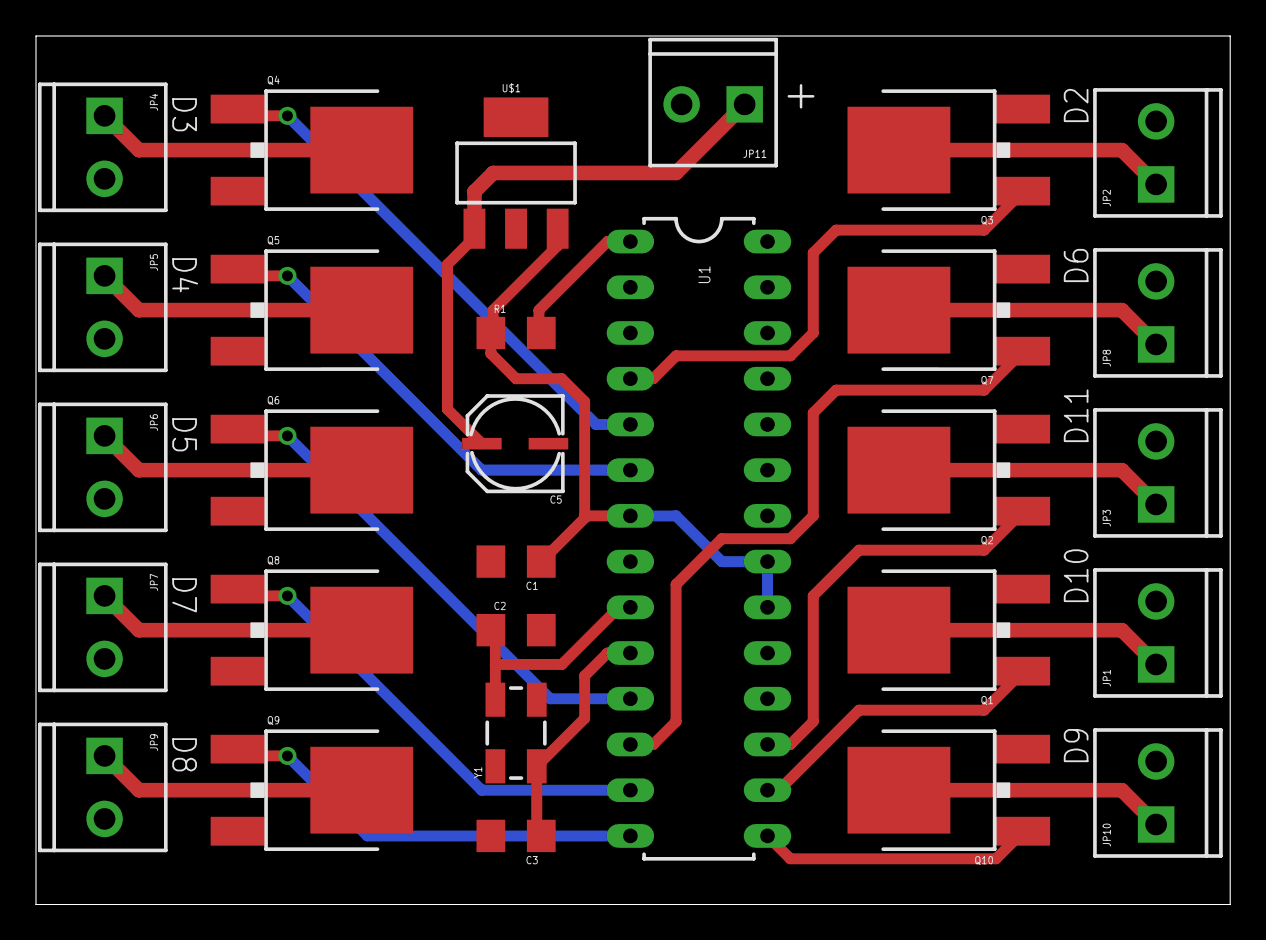
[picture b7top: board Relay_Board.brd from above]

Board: 2 copper layers, 66.3 x 48.2 mm, 29 parts (0 on the bottom side), 26 nets.

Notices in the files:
2015/Hardware/MRDT0003C1.brd:
(C) 2015
parts and their libraries:
SparkFun-Connectors: Licensing: CC v3.0 Share-Alike You are welcome to use this library for commercial purposes.
SparkFun-DiscreteSemi: Licensing: Creative Commons ShareAlike 4.0 International - https://creativecommons.org/licenses/by-sa/4.0
